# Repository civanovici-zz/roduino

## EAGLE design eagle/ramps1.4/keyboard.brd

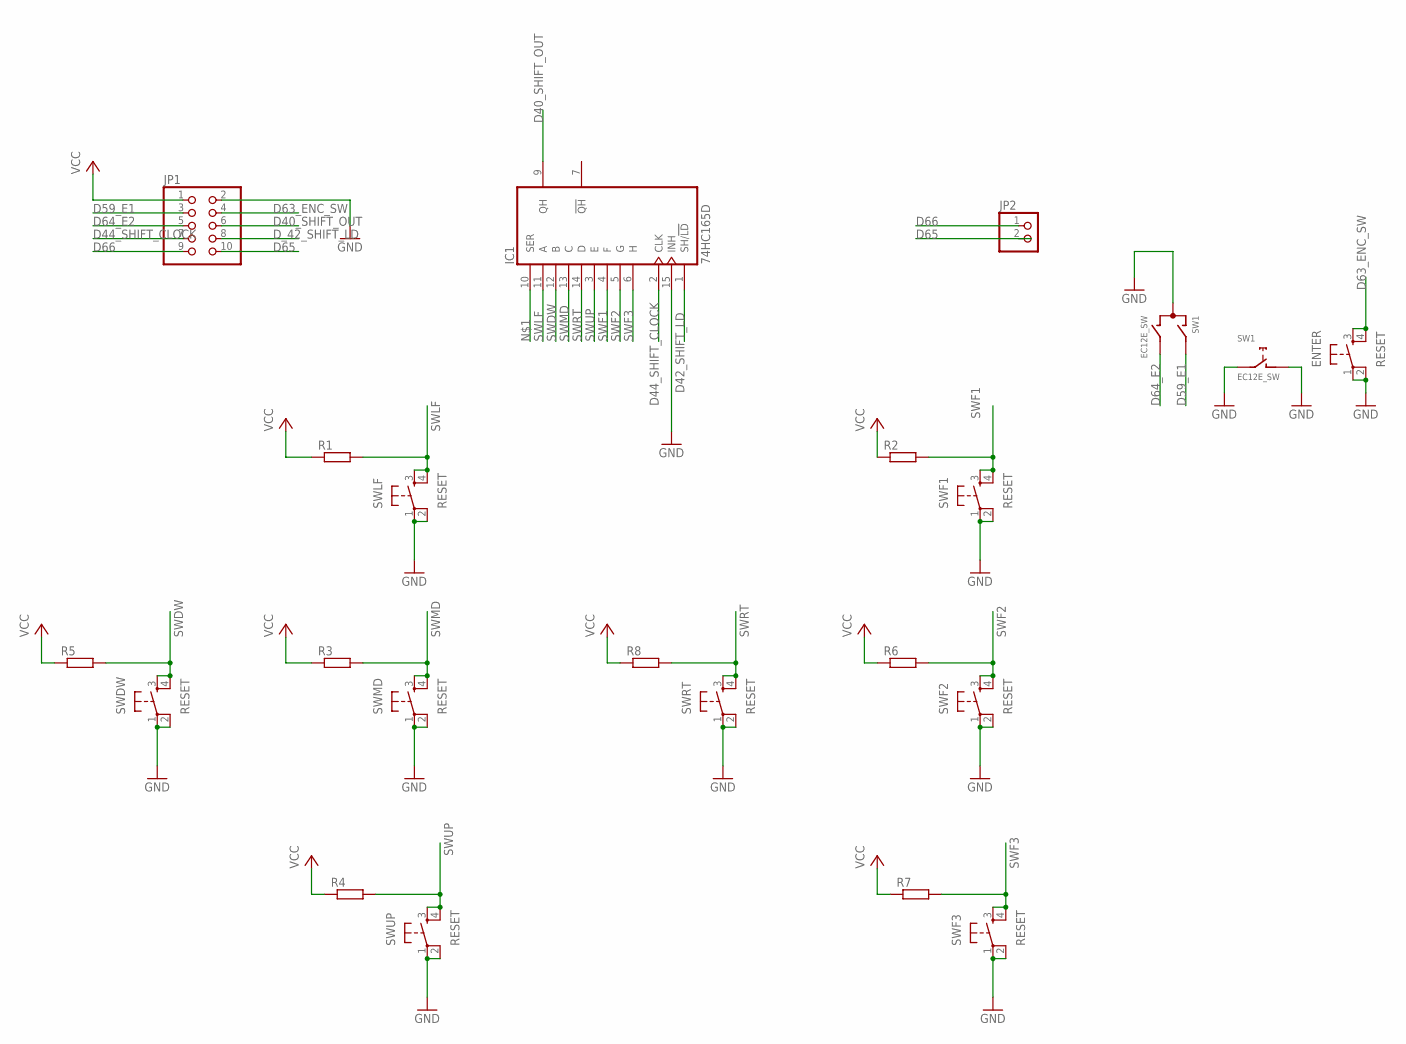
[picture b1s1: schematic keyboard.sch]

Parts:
ENTER: RESET; TACTILE-PTH
IC1: 74HC165D; SO16
JP1: PINHD-2X5; 2X05
JP2: PINHD-1X2; 1X02
R1, R2, R3, R4, R5, R6, R7, R8: R-EU_R0603; R0603
SW1: EC12E_SW; ALPS_EC12E_SW
SWDW: RESET; TACTILE-PTH
SWF1, SWF2, SWF3: RESET; TACTILE-PTH
SWLF: RESET; TACTILE-PTH
SWMD: RESET; TACTILE-PTH
SWRT: RESET; TACTILE-PTH
SWUP: RESET; TACTILE-PTH

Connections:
D40_SHIFT_OUT: IC1.9 (QH), JP1.6
D42_SHIFT_LD: IC1.1 (SH/!LD)
D44_SHIFT_CLOCK: IC1.2 (CLK), JP1.7
D59_E1: JP1.3, SW1.A
D63_ENC_SW: ENTER.3, ENTER.4, JP1.4
D64_E2: JP1.5, SW1.B
D65: JP1.10
D66: JP1.9, JP2.1
D_42_SHIFT_LD: JP1.8
GND: ENTER.1, ENTER.2, IC1.8 (GND), IC1.15 (INH), JP1.2, SW1.C, SW1.D (1), SW1.E (2), SWDW.1, SWDW.2, SWF1.1, SWF1.2, SWF2.1, SWF2.2, SWF3.1, SWF3.2, SWLF.1, SWLF.2, SWMD.1, SWMD.2, SWRT.1, SWRT.2, SWUP.1, SWUP.2
SWDW: IC1.12 (B), R5.2, SWDW.3, SWDW.4
SWF1: IC1.4 (F), R2.2, SWF1.3, SWF1.4
SWF2: IC1.5 (G), R6.2, SWF2.3, SWF2.4
SWF3: IC1.6 (H), R7.2, SWF3.3, SWF3.4
SWLF: IC1.11 (A), R1.2, SWLF.3, SWLF.4
SWMD: IC1.13 (C), R3.2, SWMD.3, SWMD.4
SWRT: IC1.14 (D), R8.2, SWRT.3, SWRT.4
SWUP: IC1.3 (E), R4.2, SWUP.3, SWUP.4
VCC: IC1.16 (VCC), JP1.1, R1.1, R2.1, R3.1, R4.1, R5.1, R6.1, R7.1, R8.1

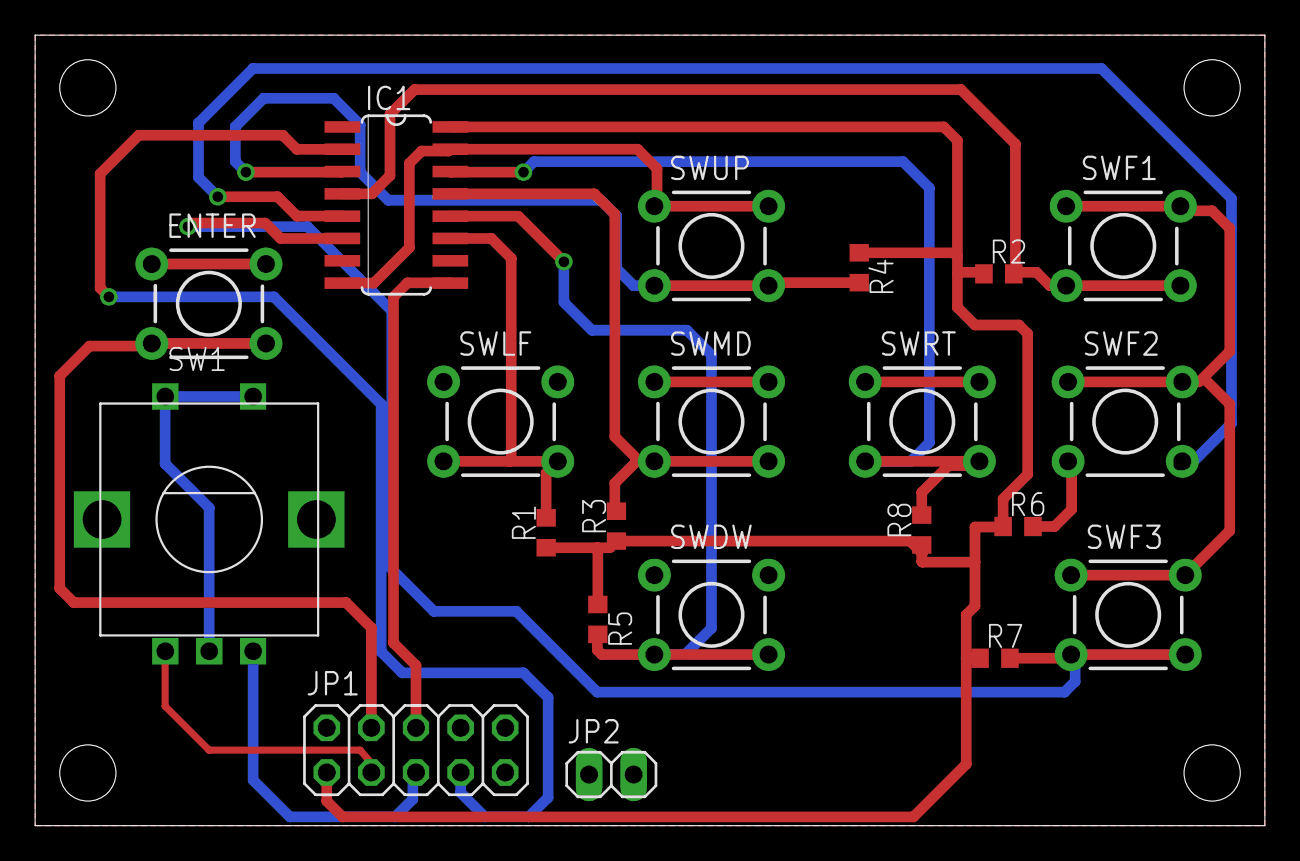
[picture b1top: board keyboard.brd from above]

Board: 2 copper layers, 70.0 x 45.0 mm, 21 parts (0 on the bottom side), 16 nets.

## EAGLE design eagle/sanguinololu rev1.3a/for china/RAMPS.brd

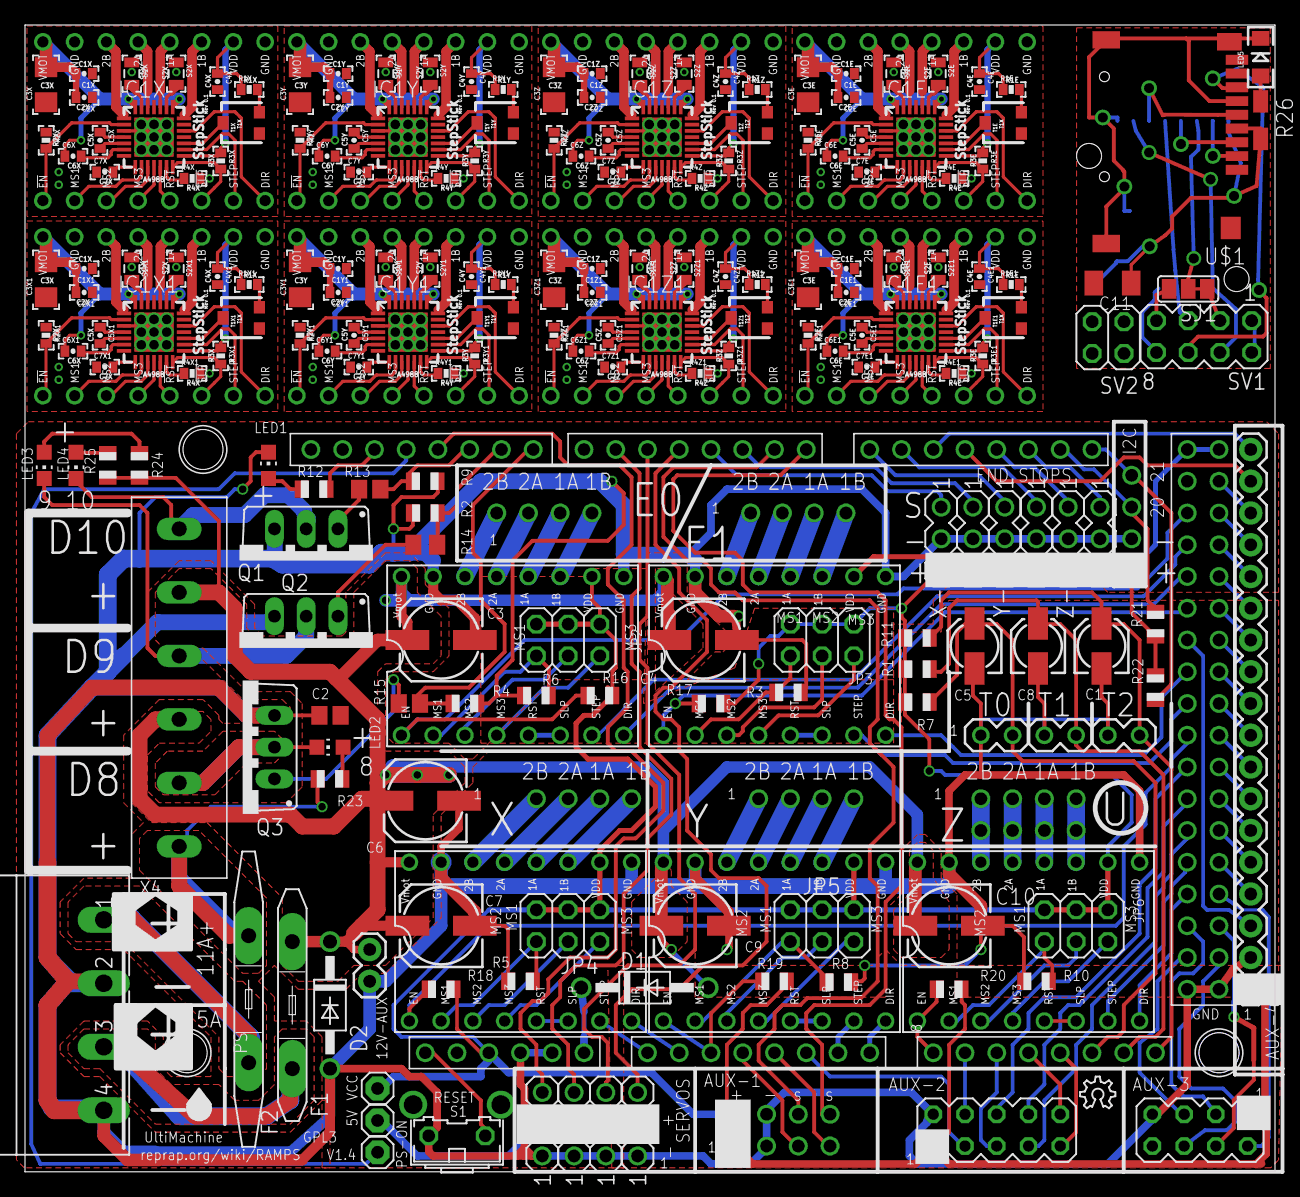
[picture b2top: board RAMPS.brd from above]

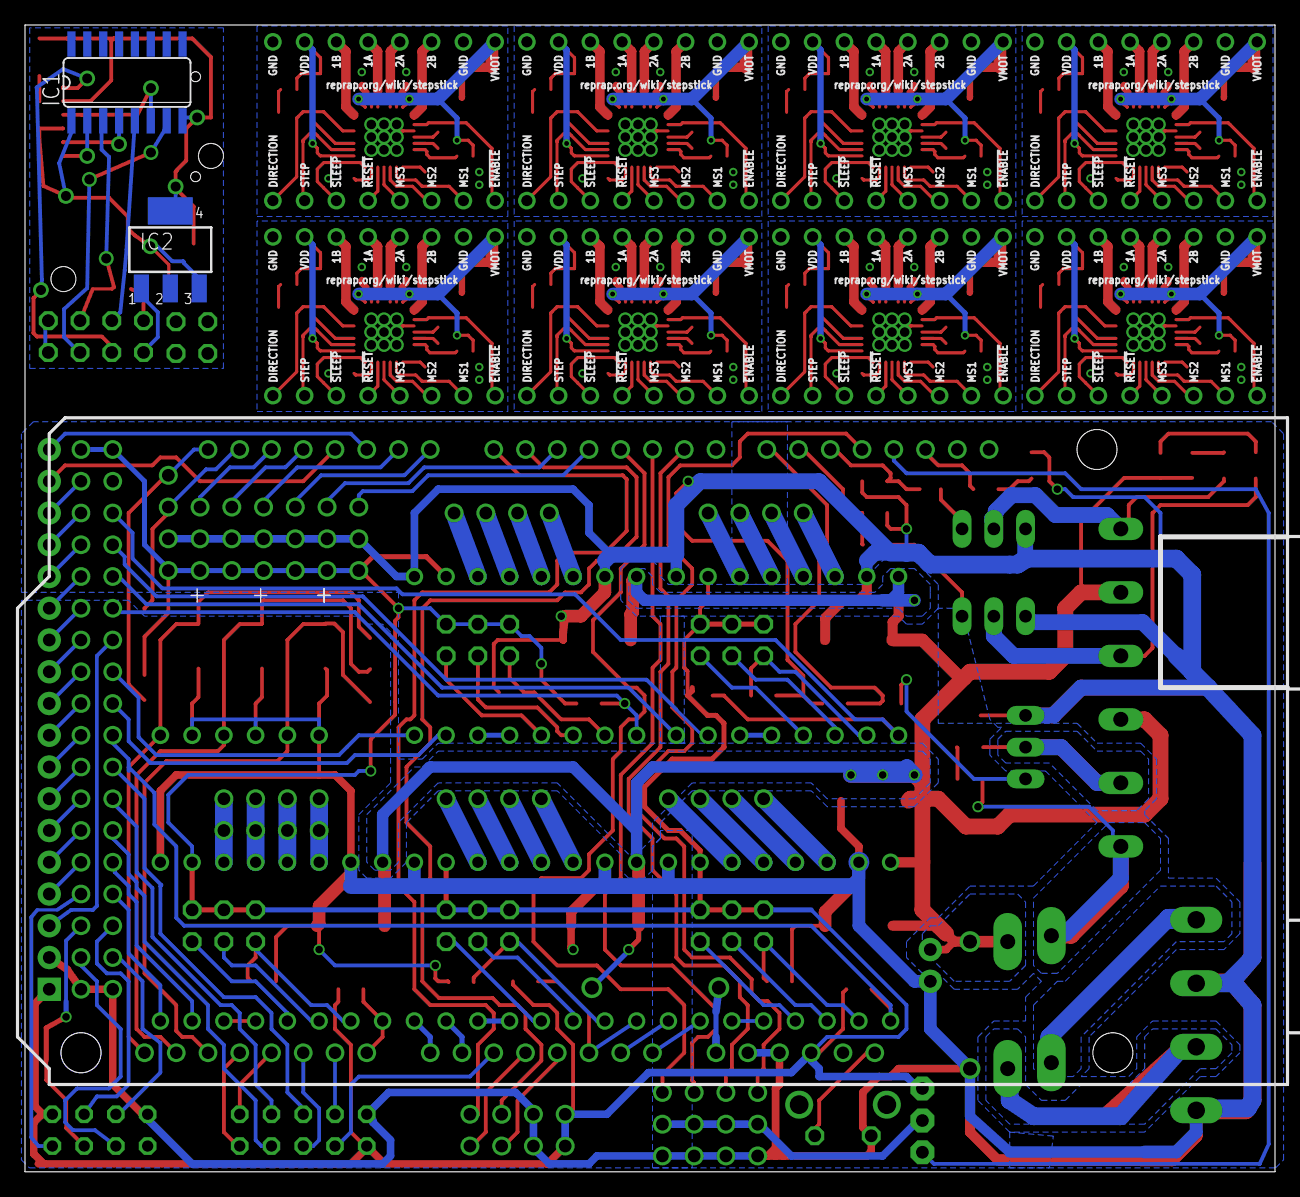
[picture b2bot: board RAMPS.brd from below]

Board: 2 copper layers, 100.0 x 91.7 mm, 225 parts (2 on the bottom side), 313 nets.

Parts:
5V: 1X01
12V-AUX: 1X02
A-OUT: 1X04
C1, C5, C8: 10uF; 153CLV-0405
C1E, C1E1, C1X, C1X1, C1Y, C1Y1, C1Z, C1Z1, C2E, C2E1, C2X, C2X1, C2Y, C2Y1, C2Z, C2Z1, C5E, C5E1, C5X, C5X1, C5Y, C5Y1, C5Z, C5Z1, C6E, C6E1, C6X, C6X1, C6Y, C6Y1, C6Z, C6Z1: .1uf; 0402-CAP
C2: 100nF; C0805
C3, C4, C6, C7, C9, C10: 100uF; 153CLV-0605
C3E, C3E1, C3X, C3X1, C3Y, C3Y1, C3Z, C3Z1: 4.7uF; 1206
C4E, C4E1, C4X, C4X1, C4Y, C4Y1, C4Z, C4Z1, C7E, C7E1, C7X, C7X1, C7Y, C7Y1, C7Z, C7Z1: .22uf; 0402-CAP
C11: C1206K
D1, D2: 1N4004; DO41-10
E0-MOT, E1-MOT: 1X04
F1: MFR500
F2: MFR1100
I2C: 1X04
IC1: 4050D; SO16
IC1E, IC1E1, IC1X, IC1X1, IC1Y, IC1Y1, IC1Z, IC1Z1: A4988; QFN28ET
IC2: LM340MP-05; SOT223
J1E, J1E1, J1X, J1X1, J1Y, J1Y1, J1Z, J1Z1: CLONOLU
JP2, JP3, JP4, JP5, JP6: 2X03
JP7: 1X06
LED1, LED2, LED3, LED4: CHIP-LED0805
LED5: LED-1206
LOGO1: OSHW_LOGO_6MILX0100-NT; OSHW_6X100_NOTEXT
PS-ON: 1X01
Q1, Q2, Q3: STP55NF06L; TO220BV
R1, R7, R11, R21, R22: 4.7K; R0805
R1E, R1E1, R1X, R1X1, R1Y, R1Y1, R1Z, R1Z1: 20k; 0402-RES
R2, R3, R4, R5, R6, R8, R9, R10: 100k; R0805
R2E, R2E1, R2X, R2X1, R2Y, R2Y1, R2Z, R2Z1, R3E, R3E1, R3X, R3X1, R3Y, R3Y1, R3Z, R3Z1: 100k; 0402-RES
R4E, R4E1, R4X, R4X1, R4Y, R4Y1, R4Z, R4Z1: 10k; 0402-RES
R12: 1K; R0805
R13, R15: 10r; R0805
R14: 10r; M0805
R16, R17, R18, R19, R20: 10k; R0805
R23, R24, R25: 1.8K; R0805
R26: R1206W
S1: B3F-31XX
S1E, S1E1, S1X, S1X1, S1Y, S1Y1, S1Z, S1Z1, S2E, S2E1, S2X, S2X1, S2Y, S2Y1, S2Z, S2Z1: 0.2; 0805
SER1, SER2, SER3, SER4: 3PIN-HEADER
SERIAL: 1X04
SJ1: SJ_2
SV1: MA04-2
SV2: 2X02
T1E, T1E1, T1X, T1X1, T1Y, T1Y1, T1Z, T1Z1: TRIM; TRIMPOT-3MM
U1: ARDUINO_MEGA_SHIELD
U$1: MICROSD_PP
U$2: 282837-6
U$3: M04X2; 2X4
U$4, U$5, U$6, U$7, U$8: A4988BREAKOUT
U$9: M18_; 1X18
U$10: M05X2; 2X5
VCC: 1X01
X4: MSTBA4
X+: 3PIN-HEADER
X-: 3PIN-HEADER
X-MOT: 1X04
Y+: 3PIN-HEADER
Y-: 3PIN-HEADER
Y-MOT: 1X04
Z+: 3PIN-HEADER
Z-: 3PIN-HEADER
Z-MOT, Z-MOT1: 1X04

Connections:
+5V: 5V.1, SER1.2, SER2.2, SER3.2, SER4.2
+12V: 12V-AUX.1, C2.1, C3.+, C4.+, C6.+, C7.+, C9.+, C10.+, D1.A, D2.C, F1.1, R24.1, R25.1, U$2.P$3, U$2.P$5, U$4.VMOT, U$5.VMOT, U$6.VMOT, U$7.VMOT, U$8.VMOT
+12V2: F2.2, R23.1, U$2.P$1
A3: SERIAL.3, U1.A3
A4: SERIAL.4, U1.A4
A5: U1.A5, U$10.3
A9: U1.A9, U$10.4
A10: U1.A10, U$10.5
A11: U1.A11, U$10.10
A12: U1.A12, U$10.9
AM-VIN: D1.C, U1.VIN
D1: A-OUT.4, U1.RX
D2: A-OUT.3, U1.TX
D4: SER4.3, U1.D4
D5: SER3.3, U1.D5
D6: SER2.3, U1.D6
D8: R4.1, R15.1, U1.D8
D9: R2.1, R14.1, U1.D9
D10: R9.1, R13.1, U1.D10
D11: SER1.3, U1.D11
D12: PS-ON.1, U1.D12
D16: U1.D16, U$9.18
D17: U1.D17, U$9.17
D23: U1.D23, U$9.16
D25: U1.D25, U$9.15
D27: U1.D27, U$9.14
D29: U1.D29, U$9.13
D31: U1.D31, U$9.12
D32: U1.D32, U$9.3
D33: U1.D33, U$9.11
D35: U1.D35, U$9.10
D37: U1.D37, U$9.9
D39: U1.D39, U$9.8
D40: U1.D40, U$10.6
D41: U1.D41, U$9.7
D42: U1.D42, U$10.8
D43: U1.D43, U$9.6
D44: U1.D44, U$10.7
D45: U1.D45, U$9.5
D47: U1.D47, U$9.4
D49: U1.D49, U$3.2
D53: U1.D53, U$3.6
E0-DIR: U1.D28, U$4.DIR
E0-EN: R16.2, U1.D24, U$4.EN
E0-STEP: U1.D26, U$4.STEP
E1-DIR: U1.D34, U$5.DIR
E1-EN: R17.2, U1.D30, U$5.EN
E1-STEP: U1.D36, U$5.STEP
ECP1: C5E.1, IC1E.4
ECP2: C5E.2, IC1E.5
ECP3: C5E1.1, IC1E1.4
ECP4: C5E1.2, IC1E1.5
EDIR: IC1E.19, J1E.DIR
EDIR1: IC1E1.19, J1E1.DIR
EENABLE: IC1E.2, J1E.!EN, R2E.2
EENABLE1: IC1E1.2, J1E1.!EN, R2E1.2
EMS1: IC1E.9, J1E.MS1
EMS2: IC1E.10, J1E.MS2
EMS3: IC1E.11, J1E.MS3
EMS4: IC1E1.9, J1E1.MS1
EMS5: IC1E1.10, J1E1.MS2
EMS6: IC1E1.11, J1E1.MS3
EOUT1A: IC1E.24, J1E.1A
EOUT1A1: IC1E1.24, J1E1.1A
EOUT1B: IC1E.21, J1E.1B
EOUT1B1: IC1E1.21, J1E1.1B
EOUT2A: IC1E.26, J1E.2A
EOUT2A1: IC1E1.26, J1E1.2A
EOUT2B: IC1E.1, J1E.2B
EOUT2B1: IC1E1.1, J1E1.2B
EREF: IC1E.17, T1E.2
EREF1: IC1E1.17, T1E1.2
EREF2: R1E.2, T1E.3
EREF3: R1E1.2, T1E1.3
ERESET: IC1E.12, J1E.!RST
ERESET1: IC1E1.12, J1E1.!RST
EROSC: IC1E.13, R4E.1
EROSC1: IC1E1.13, R4E1.1
ESENSE1: IC1E.23, S2E.2
ESENSE2: IC1E.27, S1E.2
ESENSE3: IC1E1.27, S1E1.2
ESENSE4: IC1E1.23, S2E1.2
ESLEEP: IC1E.14, J1E.!SLP, R3E.2
ESLEEP1: IC1E1.14, J1E1.!SLP, R3E1.2
ESTEP: IC1E.16, J1E.STEP
ESTEP1: IC1E1.16, J1E1.STEP
EVCP: C6E.2, IC1E.6
EVCP1: C6E1.2, IC1E1.6
EVREG: C7E.2, IC1E.8
EVREG1: C7E1.2, IC1E1.8
GND: 12V-AUX.2, A-OUT.2, C1.-, C2.2, C3.-, C4.-, C5.-, C6.-, C7.-, C8.-, C9.-, C10.-, D2.A, I2C.2, JP7.1, JP7.3, JP7.5, LED1.C, Q1.S, Q2.S, Q3.S, R2.2, R3.2, R4.2, R5.2, R6.1, R8.2, R9.2, R10.2, S1.1, SER1.1, SER2.1, SER3.1, SER4.1, SERIAL.2, U1.GND@0, U1.GND@1, U1.GND@3, U1.GND@4, U$3.7, U$4.GND, U$4.GND@0, U$5.GND, U$5.GND@0, U$6.GND, U$6.GND@0, U$7.GND, U$7.GND@0, U$8.GND, U$8.GND@0, U$9.2, U$10.2, X4.2, X4.4, X+.2, X-.2, Y+.2, Y-.2, Z+.2, Z-.2
GND1: C1E.1, C1X.1, C1Y.1, C1Z.1, C2E.1, C2X.1, C2Y.1, C2Z.1, C3E.1, C3X.1, C3Y.1, C3Z.1, C4E.2, C4X.2, C4Y.2, C4Z.2, C7E.1, C7X.1, C7Y.1, C7Z.1, IC1E.3, IC1E.7, IC1E.18, IC1E.20, IC1E.25, IC1E.EXP, IC1X.3, IC1X.7, IC1X.18, IC1X.20, IC1X.25, IC1X.EXP, IC1Y.3, IC1Y.7, IC1Y.18, IC1Y.20, IC1Y.25, IC1Y.EXP, IC1Z.3, IC1Z.7, IC1Z.18, IC1Z.20, IC1Z.25, IC1Z.EXP, J1E.GND$1, J1E.GND$2, J1X.GND$1, J1X.GND$2, J1Y.GND$1, J1Y.GND$2, J1Z.GND$1, J1Z.GND$2, R2E.1, R2X.1, R2Y.1, R2Z.1, R4E.2, R4X.2, R4Y.2, R4Z.2, S1E.1, S1X.1, S1Y.1, S1Z.1, S2E.1, S2X.1, S2Y.1, S2Z.1, T1E.1, T1X.1, T1Y.1, T1Z.1
GND2: C1E1.1, C1X1.1, C1Y1.1, C1Z1.1, C2E1.1, C2X1.1, C2Y1.1, C2Z1.1, C3E1.1, C3X1.1, C3Y1.1, C3Z1.1, C4E1.2, C4X1.2, C4Y1.2, C4Z1.2, C7E1.1, C7X1.1, C7Y1.1, C7Z1.1, IC1E1.3, IC1E1.7, IC1E1.18, IC1E1.20, IC1E1.25, IC1E1.EXP, IC1X1.3, IC1X1.7, IC1X1.18, IC1X1.20, IC1X1.25, IC1X1.EXP, IC1Y1.3, IC1Y1.7, IC1Y1.18, IC1Y1.20, IC1Y1.25, IC1Y1.EXP, IC1Z1.3, IC1Z1.7, IC1Z1.18, IC1Z1.20, IC1Z1.25, IC1Z1.EXP, J1E1.GND$1, J1E1.GND$2, J1X1.GND$1, J1X1.GND$2, J1Y1.GND$1, J1Y1.GND$2, J1Z1.GND$1, J1Z1.GND$2, R2E1.1, R2X1.1, R2Y1.1, R2Z1.1, R4E1.2, R4X1.2, R4Y1.2, R4Z1.2, S1E1.1, S1X1.1, S1Y1.1, S1Z1.1, S2E1.1, S2X1.1, S2Y1.1, S2Z1.1, T1E1.1, T1X1.1, T1Y1.1, T1Z1.1
GND3: C11.2, IC1.8, IC2.4, LED5.C, SV1.1, SV1.2, U$1.6, U$1.GND@1, U$1.GND@2, U$1.GND@3, U$1.GND@4
LED: R12.2, U1.D13
MISO: U1.D50, U$3.3
MOSI: U1.D51, U$3.4
unnamed: LED3.C, Q2.D, U$2.P$4
unnamed: IC1.2, U$1.2
unnamed: E0-MOT.1, U$4.2B
unnamed: E0-MOT.2, U$4.2A
unnamed: JP2.1, R6.2, U$4.MS1
unnamed: JP2.5, U$4.MS3
unnamed: LED4.C, Q1.D, U$2.P$6
unnamed: U$4.RST, U$4.SLP
unnamed: JP2.3, U$4.MS2
unnamed: E0-MOT.3, U$4.1A
unnamed: E0-MOT.4, U$4.1B
unnamed: E1-MOT.1, U$5.2B
unnamed: E1-MOT.2, U$5.2A
unnamed: JP4.1, R5.1, U$6.MS1
unnamed: JP4.3, U$6.MS2
unnamed: E1-MOT.3, U$5.1A
unnamed: JP5.3, U$7.MS2
unnamed: E1-MOT.4, U$5.1B
unnamed: JP4.5, U$6.MS3
unnamed: U$6.RST, U$6.SLP
unnamed: U$6.2B, X-MOT.1
unnamed: U$6.2A, X-MOT.2
unnamed: U$7.RST, U$7.SLP
unnamed: U$5.RST, U$5.SLP
unnamed: JP3.1, R3.1, U$5.MS1
unnamed: U$6.1A, X-MOT.3
unnamed: U$6.1B, X-MOT.4
unnamed: U$7.2B, Y-MOT.1
unnamed: U$7.2A, Y-MOT.2
unnamed: U$7.1A, Y-MOT.3
unnamed: JP5.5, U$7.MS3
unnamed: LED2.A, R23.2
unnamed: JP5.1, R8.1, U$7.MS1
unnamed: JP3.5, U$5.MS3
unnamed: JP3.3, U$5.MS2
unnamed: U$7.1B, Y-MOT.4
unnamed: JP6.3, U$8.MS2
unnamed: U$8.RST, U$8.SLP
unnamed: JP6.5, U$8.MS3
unnamed: JP6.1, R10.1, U$8.MS1
unnamed: U$8.2B, Z-MOT.1, Z-MOT1.1
unnamed: U$8.2A, Z-MOT.2, Z-MOT1.2
unnamed: U$8.1A, Z-MOT.3, Z-MOT1.3
unnamed: U$8.1B, Z-MOT.4, Z-MOT1.4
unnamed: LED3.A, R24.2
unnamed: LED1.A, R12.1
unnamed: Q2.G, R14.2
unnamed: Q1.G, R13.2
unnamed: Q3.G, R15.2
unnamed: LED4.A, R25.2
unnamed: LED2.C, Q3.D, U$2.P$2
unnamed: IC1.4, U$1.3
unnamed: F2.1, X4.1
unnamed: F1.2, X4.3
unnamed: IC1.6, U$1.5
unnamed: SV1.6, U$1.7
unnamed: IC1.7, SV1.4
unnamed: IC1.5, SV1.5
unnamed: SJ1.3, SV1.7
unnamed: IC1.3, SJ1.1, SJ1.2, SV1.3
unnamed: IC2.1, SV1.8
unnamed: LED5.A, R26.1
RESET: S1.2, U1.RES
SCK: U1.D52, U$3.5
SCL: I2C.4, R22.1, U1.D21
SDA: I2C.3, R21.1, U1.D20
THERM0: C5.+, JP7.2, R7.1, U1.A13
THERM1: C8.+, JP7.4, R1.1, U1.A14
THERM2: C1.+, JP7.6, R11.1, U1.A15
VCC: A-OUT.1, I2C.1, JP2.2, JP2.4, JP2.6, JP3.2, JP3.4, JP3.6, JP4.2, JP4.4, JP4.6, JP5.2, JP5.4, JP5.6, JP6.2, JP6.4, JP6.6, R1.2, R7.2, R11.2, R16.1, R17.1, R18.1, R19.1, R20.1, R21.2, R22.2, SERIAL.1, U1.5V@0, U1.5V@1, U1.5V@2, U$3.1, U$4.VDD, U$5.VDD, U$6.VDD, U$7.VDD, U$8.VDD, U$9.1, U$10.1, VCC.1, X+.3, X-.3, Y+.3, Y-.3, Z+.3, Z-.3
VCC1: C11.1, IC1.1, IC2.3, R26.2, U$1.4
VDD: C4E.1, C4X.1, C4Y.1, C4Z.1, IC1E.15, IC1X.15, IC1Y.15, IC1Z.15, J1E.VDD, J1X.VDD, J1Y.VDD, J1Z.VDD, R1E.1, R1X.1, R1Y.1, R1Z.1, R3E.1, R3X.1, R3Y.1, R3Z.1
VDD1: C4E1.1, C4X1.1, C4Y1.1, C4Z1.1, IC1E1.15, IC1X1.15, IC1Y1.15, IC1Z1.15, J1E1.VDD, J1X1.VDD, J1Y1.VDD, J1Z1.VDD, R1E1.1, R1X1.1, R1Y1.1, R1Z1.1, R3E1.1, R3X1.1, R3Y1.1, R3Z1.1
VMOT: C1E.2, C1X.2, C1Y.2, C1Z.2, C2E.2, C2X.2, C2Y.2, C2Z.2, C3E.2, C3X.2, C3Y.2, C3Z.2, C6E.1, C6X.1, C6Y.1, C6Z.1, IC1E.22, IC1E.28, IC1X.22, IC1X.28, IC1Y.22, IC1Y.28, IC1Z.22, IC1Z.28, J1E.VMOT, J1X.VMOT, J1Y.VMOT, J1Z.VMOT
VMOT1: C1E1.2, C1X1.2, C1Y1.2, C1Z1.2, C2E1.2, C2X1.2, C2Y1.2, C2Z1.2, C3E1.2, C3X1.2, C3Y1.2, C3Z1.2, C6E1.1, C6X1.1, C6Y1.1, C6Z1.1, IC1E1.22, IC1E1.28, IC1X1.22, IC1X1.28, IC1Y1.22, IC1Y1.28, IC1Z1.22, IC1Z1.28, J1E1.VMOT, J1X1.VMOT, J1Y1.VMOT, J1Z1.VMOT
X-DIR: U1.A1, U$6.DIR
X-EN: R18.2, U1.D38, U$6.EN
X-MAX: U1.D2, X+.1
X-MIN: U1.D3, X-.1
X-STEP: U1.A0, U$6.STEP
XCP1: C5X.1, IC1X.4
XCP2: C5X.2, IC1X.5
XCP3: C5X1.1, IC1X1.4
XCP4: C5X1.2, IC1X1.5
XDIR: IC1X.19, J1X.DIR
XDIR1: IC1X1.19, J1X1.DIR
XENABLE: IC1X.2, J1X.!EN, R2X.2
XENABLE1: IC1X1.2, J1X1.!EN, R2X1.2
XMS1: IC1X.9, J1X.MS1
XMS2: IC1X.10, J1X.MS2
XMS3: IC1X.11, J1X.MS3
XMS4: IC1X1.9, J1X1.MS1
XMS5: IC1X1.10, J1X1.MS2
XMS6: IC1X1.11, J1X1.MS3
XOUT1A: IC1X.24, J1X.1A
XOUT1A1: IC1X1.24, J1X1.1A
XOUT1B: IC1X.21, J1X.1B
XOUT1B1: IC1X1.21, J1X1.1B
XOUT2A: IC1X.26, J1X.2A
XOUT2A1: IC1X1.26, J1X1.2A
XOUT2B: IC1X.1, J1X.2B
XOUT2B1: IC1Y.1, J1Y.2B
XOUT2B2: IC1X1.1, J1X1.2B
XOUT2B3: IC1Y1.1, J1Y1.2B
XREF: IC1X.17, T1X.2
XREF1: IC1X1.17, T1X1.2
XREF2: R1X.2, T1X.3
XREF3: R1X1.2, T1X1.3
XRESET: IC1X.12, J1X.!RST
XRESET1: IC1X1.12, J1X1.!RST
XROSC: IC1X.13, R4X.1
XROSC1: IC1X1.13, R4X1.1
XSENSE1: IC1X.23, S2X.2
XSENSE2: IC1X.27, S1X.2
XSENSE3: IC1X1.27, S1X1.2
XSENSE4: IC1X1.23, S2X1.2
XSLEEP: IC1X.14, J1X.!SLP, R3X.2
XSLEEP1: IC1X1.14, J1X1.!SLP, R3X1.2
XSTEP: IC1X.16, J1X.STEP
XSTEP1: IC1X1.16, J1X1.STEP
XVCP: C6X.2, IC1X.6
XVCP1: C6X1.2, IC1X1.6
XVREG: C7X.2, IC1X.8
XVREG1: C7X1.2, IC1X1.8
Y-DIR: U1.A7, U$7.DIR
Y-EN: R19.2, U1.A2, U$7.EN
Y-MAX: U1.D15, Y+.1
Y-MIN: U1.D14, Y-.1
Y-STEP: U1.A6, U$7.STEP
YCP1: C5Y.1, IC1Y.4
YCP2: C5Y.2, IC1Y.5
YCP3: C5Y1.1, IC1Y1.4
YCP4: C5Y1.2, IC1Y1.5
YDIR1: IC1Y.19, J1Y.DIR
YDIR2: IC1Y1.19, J1Y1.DIR
YENABLE: IC1Y.2, J1Y.!EN, R2Y.2
YENABLE1: IC1Y1.2, J1Y1.!EN, R2Y1.2
YMS1: IC1Y.9, J1Y.MS1
YMS2: IC1Y.10, J1Y.MS2
YMS3: IC1Y.11, J1Y.MS3
YMS4: IC1Y1.9, J1Y1.MS1
YMS5: IC1Y1.10, J1Y1.MS2
YMS6: IC1Y1.11, J1Y1.MS3
YOUT1A: IC1Y.24, J1Y.1A
YOUT1A1: IC1Y1.24, J1Y1.1A
YOUT1B: IC1Y.21, J1Y.1B
YOUT1B1: IC1Y1.21, J1Y1.1B
YOUT2A: IC1Y.26, J1Y.2A
YOUT2A1: IC1Y1.26, J1Y1.2A
YREF: IC1Y.17, T1Y.2
YREF1: R1Y.2, T1Y.3
YREF2: IC1Y1.17, T1Y1.2
YREF3: R1Y1.2, T1Y1.3
YRESET: IC1Y.12, J1Y.!RST
YRESET1: IC1Y1.12, J1Y1.!RST
YROSC: IC1Y.13, R4Y.1
YROSC1: IC1Y1.13, R4Y1.1
YSENSE1: IC1Y.23, S2Y.2
YSENSE2: IC1Y.27, S1Y.2
YSENSE3: IC1Y1.27, S1Y1.2
YSENSE4: IC1Y1.23, S2Y1.2
YSLEEP: IC1Y.14, J1Y.!SLP, R3Y.2
YSLEEP1: IC1Y1.14, J1Y1.!SLP, R3Y1.2
YSTEP: IC1Y.16, J1Y.STEP
YSTEP1: IC1Y1.16, J1Y1.STEP
YVCP: C6Y.2, IC1Y.6
YVCP1: C6Y1.2, IC1Y1.6
YVREG: C7Y.2, IC1Y.8
YVREG1: C7Y1.2, IC1Y1.8
Z-DIR: U1.D48, U$8.DIR
Z-EN: R20.2, U1.A8, U$8.EN
Z-MAX: U1.D19, Z+.1
Z-MIN: U1.D18, Z-.1
Z-STEP: U1.D46, U$8.STEP
ZCP1: C5Z.1, IC1Z.4
ZCP2: C5Z.2, IC1Z.5
ZCP3: C5Z1.1, IC1Z1.4
ZCP4: C5Z1.2, IC1Z1.5
ZDIR: IC1Z.19, J1Z.DIR
ZDIR1: IC1Z1.19, J1Z1.DIR
ZENABLE: IC1Z.2, J1Z.!EN, R2Z.2
ZENABLE1: IC1Z1.2, J1Z1.!EN, R2Z1.2
ZMS1: IC1Z.9, J1Z.MS1
ZMS2: IC1Z.10, J1Z.MS2
ZMS3: IC1Z.11, J1Z.MS3
ZMS4: IC1Z1.9, J1Z1.MS1
ZMS5: IC1Z1.10, J1Z1.MS2
ZMS6: IC1Z1.11, J1Z1.MS3
ZOUT1A: IC1Z.24, J1Z.1A
ZOUT1A1: IC1Z1.24, J1Z1.1A
ZOUT1B: IC1Z.21, J1Z.1B
ZOUT1B1: IC1Z1.21, J1Z1.1B
ZOUT2A: IC1Z.26, J1Z.2A
ZOUT2A1: IC1Z1.26, J1Z1.2A
ZOUT2B: IC1Z.1, J1Z.2B
ZOUT2B1: IC1Z1.1, J1Z1.2B
ZREF: IC1Z.17, T1Z.2
ZREF1: IC1Z1.17, T1Z1.2
ZREF2: R1Z.2, T1Z.3
ZREF3: R1Z1.2, T1Z1.3
ZRESET: IC1Z.12, J1Z.!RST
ZRESET1: IC1Z1.12, J1Z1.!RST
ZROSC: IC1Z.13, R4Z.1
ZROSC1: IC1Z1.13, R4Z1.1
ZSENSE1: IC1Z.23, S2Z.2
ZSENSE2: IC1Z.27, S1Z.2
ZSENSE3: IC1Z1.27, S1Z1.2
ZSENSE4: IC1Z1.23, S2Z1.2
ZSLEEP: IC1Z.14, J1Z.!SLP, R3Z.2
ZSLEEP1: IC1Z1.14, J1Z1.!SLP, R3Z1.2
ZSTEP: IC1Z.16, J1Z.STEP
ZSTEP1: IC1Z1.16, J1Z1.STEP
ZVCP: C6Z.2, IC1Z.6
ZVCP1: C6Z1.2, IC1Z1.6
ZVREG: C7Z.2, IC1Z.8
ZVREG1: C7Z1.2, IC1Z1.8

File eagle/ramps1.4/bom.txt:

Partlist

Exported from RAMPS_1-41.sch at 11/4/2012 11:36:24 PM

EAGLE Version 6.3.0 Copyright (c) 1988-2012 CadSoft

Assembly variant: 

Part     Value               Device              Package             Library          Sheet

5V                           PINHD-1X1           1X01                adafruit         1
12V-AUX                      M02PTH              1X02                SparkFun         1
A-OUT                        PINHD-1X4           1X04                RepRapjr         1
C1       10uF                CPOL-US153CLV-0405  153CLV-0405         adafruit         1
C2       100nF               C-EUC0805           C0805               resistor         1
C3       100uF               CPOL-US153CLV-0605  153CLV-0605         adafruit         1
C4       100uF               CPOL-US153CLV-0605  153CLV-0605         adafruit         1
C5       10uF                CPOL-US153CLV-0405  153CLV-0405         adafruit         1
C6       100uF               CPOL-US153CLV-0605  153CLV-0605         adafruit         1
C7       100uF               CPOL-US153CLV-0605  153CLV-0605         adafruit         1
C8       10uF                CPOL-US153CLV-0405  153CLV-0405         adafruit         1
C9       100uF               CPOL-US153CLV-0605  153CLV-0605         adafruit         1
C10      100uF               CPOL-US153CLV-0605  153CLV-0605         adafruit         1
D1       1N4004              1N4004              DO41-10             diode            1
D2       1N4004              1N4004              DO41-10             diode            1
E0-MOT                       PINHD-1X4           1X04                RepRapjr         1
E1-MOT                       PINHD-1X4           1X04                RepRapjr         1
F1       MFR500              PTCFUSE             MFR500              RepRapjr         1
F2       MFR1100             PTCFUSEMFR1100      MFR1100             RepRapjr         1
I2C                          PINHD-1X4           1X04                RepRapjr         1
JP2                          PINHD-2X3           2X03                pinhead          1
JP3                          PINHD-2X3           2X03                pinhead          1
JP4                          PINHD-2X3           2X03                pinhead          1
JP5                          PINHD-2X3           2X03                pinhead          1
JP6                          PINHD-2X3           2X03                pinhead          1
JP7                          M06SIP              1X06                SparkFun         1
LED1                         LEDCHIP-LED0805     CHIP-LED0805        led              1
LED2                         LEDCHIP-LED0805     CHIP-LED0805        led              1
LED3                         LEDCHIP-LED0805     CHIP-LED0805        led              1
LED4                         LEDCHIP-LED0805     CHIP-LED0805        led              1
PS-ON                        PINHD-1X1           1X01                adafruit         1
Q1       STP55NF06L          IRF512              TO220BV             transistor-power 1
Q2       STP55NF06L          IRF512              TO220BV             transistor-power 1
Q3       STP55NF06L          IRF512              TO220BV             transistor-power 1
R1       4.7K                R-US_R0805          R0805               adafruit         1
R2       100k                R-US_R0805          R0805               adafruit         1
R3       100k                R-US_R0805          R0805               adafruit         1
R4       100k                R-US_R0805          R0805               adafruit         1
R5       100k                R-US_R0805          R0805               adafruit         1
R6       100k                R-US_R0805          R0805               adafruit         1
R7       4.7K                R-US_R0805          R0805               adafruit         1
R8       100k                R-US_R0805          R0805               adafruit         1
R9       100k                R-US_R0805          R0805               adafruit         1
R10      100k                R-US_R0805          R0805               adafruit         1
R11      4.7K                R-US_R0805          R0805               adafruit         1
R12      1K                  R-US_R0805          R0805               adafruit         1
R13      10r                 R-US_R0805          R0805               resistor         1
R14      10r                 R-US_M0805          M0805               resistor         1
R15      10r                 R-US_R0805          R0805               resistor         1
R16      10k                 R-US_R0805          R0805               adafruit         1
R17      10k                 R-US_R0805          R0805               adafruit         1
R18      10k                 R-US_R0805          R0805               adafruit         1
R19      10k                 R-US_R0805          R0805               adafruit         1
R20      10k                 R-US_R0805          R0805               adafruit         1
R21      4.7K                R-US_R0805          R0805               adafruit         1
R22      4.7K                R-US_R0805          R0805               adafruit         1
R23      1.8K                R-US_R0805          R0805               adafruit         1
R24      1.8K                R-US_R0805          R0805               adafruit         1
R25      1.8K                R-US_R0805          R0805               adafruit         1
S1                           31-XX               B3F-31XX            switch-omron     1
SER1                         3PIN-HEADER         3PIN-HEADER         ultimachine      1
SER2                         3PIN-HEADER         3PIN-HEADER         ultimachine      1
SER3                         3PIN-HEADER         3PIN-HEADER         ultimachine      1
SER4                         3PIN-HEADER         3PIN-HEADER         ultimachine      1
SERIAL                       PINHD-1X4           1X04                RepRapjr         1
U$2      282837-6            282837-6            282837-6            RepRapjr         1
U$3      M04X2               M04X2               2X4                 SparkFun         1
U$4      A4988BREAKOUT       A4988BREAKOUT       A4988BREAKOUT       RepRapjr         1
U$5      A4988BREAKOUT       A4988BREAKOUT       A4988BREAKOUT       RepRapjr         1
U$6      A4988BREAKOUT       A4988BREAKOUT       A4988BREAKOUT       RepRapjr         1
U$7      A4988BREAKOUT       A4988BREAKOUT       A4988BREAKOUT       RepRapjr         1
U$8      A4988BREAKOUT       A4988BREAKOUT       A4988BREAKOUT       RepRapjr         1
U$9      M18_                M18_                1X18                SparkFun         1
U$10     M05X2               M05X2               2X5                 RepRapjr         1
U1       ARDUINO_MEGA_SHIELD ARDUINO_MEGA_SHIELD ARDUINO_MEGA_SHIELD RepRapjr         1
VCC                          PINHD-1X1           1X01                adafruit         1
X+                           3PIN-HEADER         3PIN-HEADER         ultimachine      1
X-                           3PIN-HEADER         3PIN-HEADER         ultimachine      1
X-MOT                        PINHD-1X4           1X04                RepRapjr         1
X4       MSTBA4              MSTBA4              MSTBA4              con-phoenix-508  1
Y+                           3PIN-HEADER         3PIN-HEADER         ultimachine      1
Y-                           3PIN-HEADER         3PIN-HEADER         ultimachine      1
Y-MOT                        PINHD-1X4           1X04                RepRapjr         1
Z+                           3PIN-HEADER         3PIN-HEADER         ultimachine      1
Z-                           3PIN-HEADER         3PIN-HEADER         ultimachine      1
Z-MOT                        PINHD-1X4           1X04                RepRapjr         1
Z-MOT1                       PINHD-1X4           1X04                RepRapjr         1

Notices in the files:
eagle/sanguinololu rev1.3a/for china/RAMPS.brd:
GPL3
